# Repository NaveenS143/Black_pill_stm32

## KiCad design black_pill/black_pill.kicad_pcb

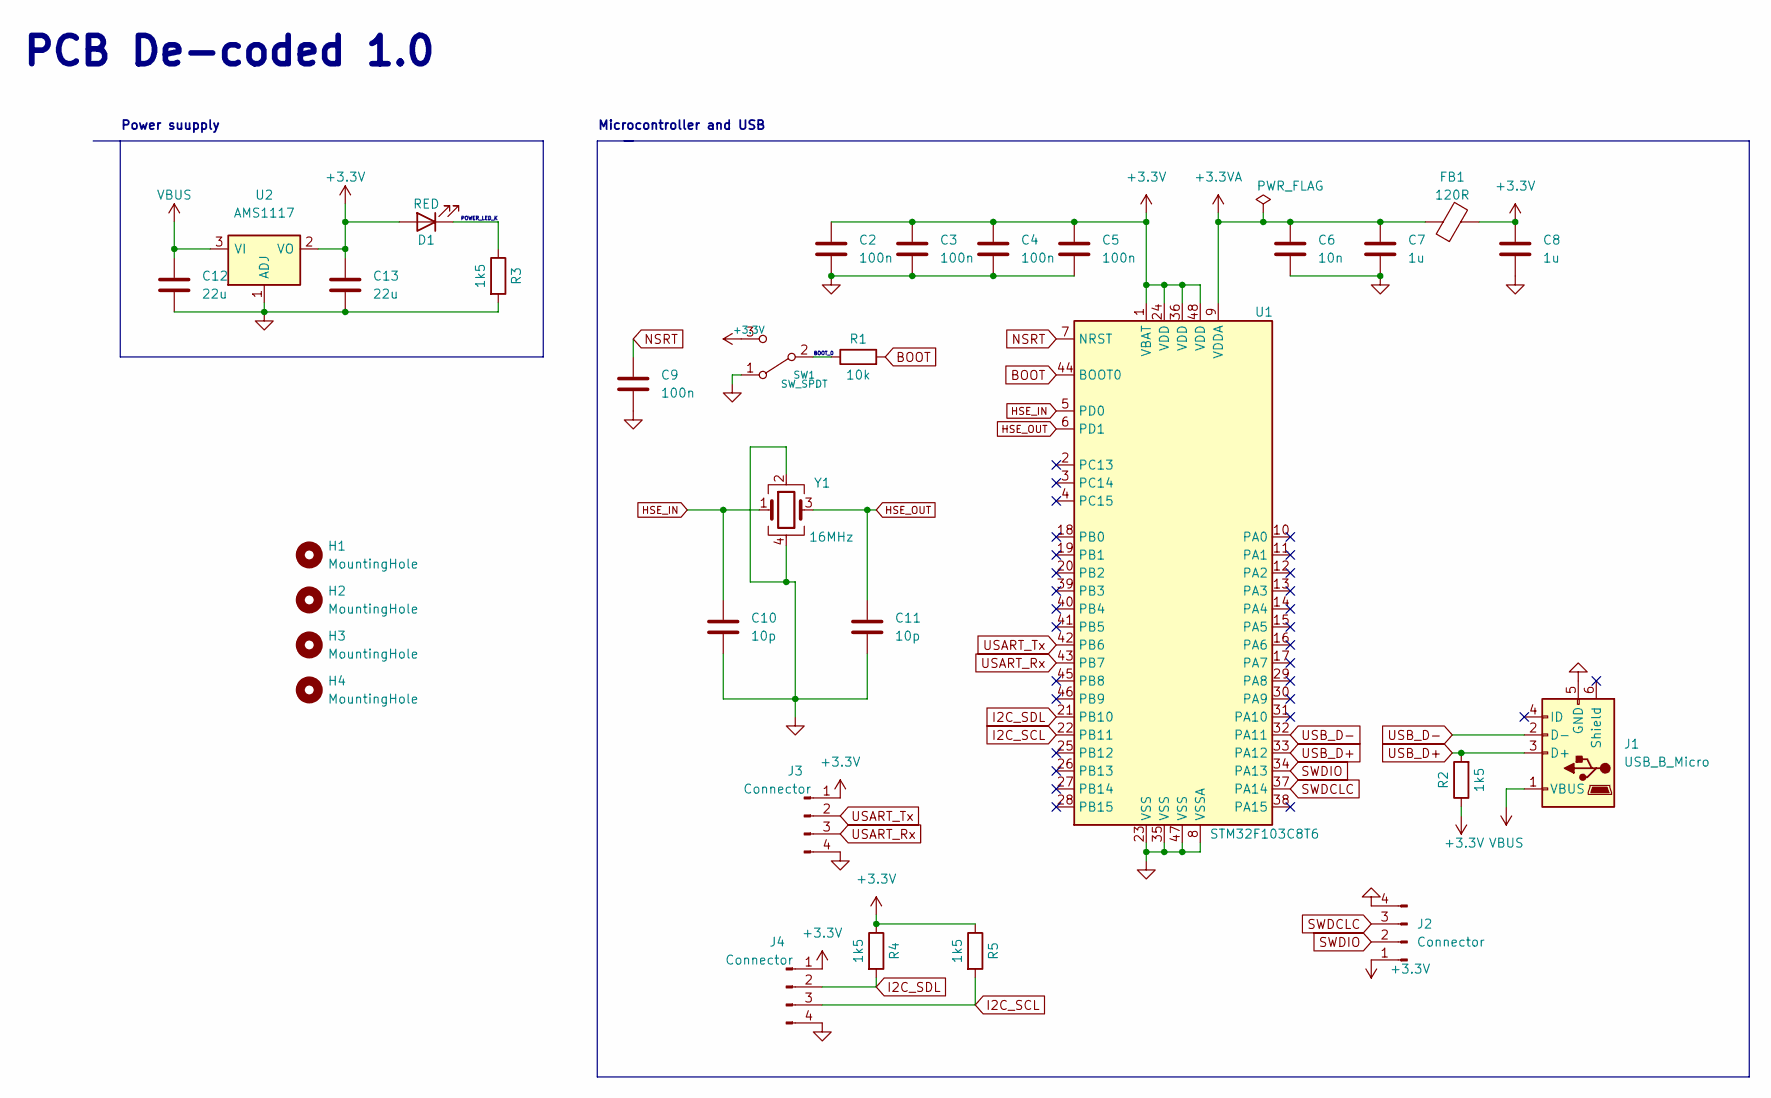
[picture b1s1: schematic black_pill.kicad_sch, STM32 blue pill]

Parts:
C2, C3, C4, C5, C9: 100n; C_0402_1005Metric
C6: 10n; C_0402_1005Metric
C7, C8: 1u; C_0402_1005Metric
C10, C11: 10p; C_0402_1005Metric
C12, C13: 22u; C_0805_2012Metric
D1: RED; LED_0603_1608Metric
FB1: 120R; L_0603_1608Metric
H1, H2, H3, H4: MountingHole; MountingHole_2.2mm_M2
J1: USB_B_Micro; USB_Micro-B_Wuerth_629105150521
J2, J3, J4: Connector; PinHeader_1x04_P2.54mm_Vertical
R1: 10k; R_0402_1005Metric
R2, R3, R4, R5: 1k5; R_0402_1005Metric
SW1: SW_SPDT; SW_SPDT_PCM12
U1: STM32F103C8T6; LQFP-48_7x7mm_P0.5mm
U2: AMS1117; SOT-223-3_TabPin2
Y1: 16MHz; Crystal_SMD_3225-4Pin_3.2x2.5mm

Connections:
+3.3VA: C6.1, C7.1, FB1.1, U1.9 (VDDA)
+3V3: C2.1, C3.1, C4.1, C5.1, C8.1, C13.1, D1.2 (A), FB1.2, J2.1, J3.1, J4.1, R2.1, R4.1, R5.1, SW1.3 (C), U1.1 (VBAT), U1.24 (VDD), U1.36 (VDD), U1.48 (VDD), U2.2 (VO)
BOOT: R1.2, U1.44 (BOOT0)
GND: C2.2, C3.2, C4.2, C5.2, C6.2, C7.2, C8.2, C9.2, C10.2, C11.2, C12.2, C13.2, J1.5 (GND), J2.4, J3.4, J4.4, R3.2, SW1.1 (A), U1.8 (VSSA), U1.23 (VSS), U1.35 (VSS), U1.47 (VSS), U2.1 (ADJ), Y1.2, Y1.4
HSE_IN: C10.1, U1.5 (PD0), Y1.1
HSE_OUT: C11.1, U1.6 (PD1), Y1.3
I2C_SCL: J4.3, R5.2, U1.22 (PB11)
I2C_SDL: J4.2, R4.2, U1.21 (PB10)
NSRT: C9.1, U1.7 (NRST)
unnamed: D1.1 (K), R3.1
unnamed: R1.1, SW1.2 (B)
SWDCLC: J2.3, U1.37 (PA14)
SWDIO: J2.2, U1.34 (PA13)
USART_Rx: J3.3, U1.43 (PB7)
USART_Tx: J3.2, U1.42 (PB6)
USB_D+: J1.3 (D+), R2.2, U1.33 (PA12)
USB_D-: J1.2 (D-), U1.32 (PA11)
VBUS: C12.1, J1.1 (VBUS), U2.3 (VI)

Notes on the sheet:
POWER_LED_K
PCB De-coded 1.0
Microcontroller and USB
BOOT_0
Power suupply

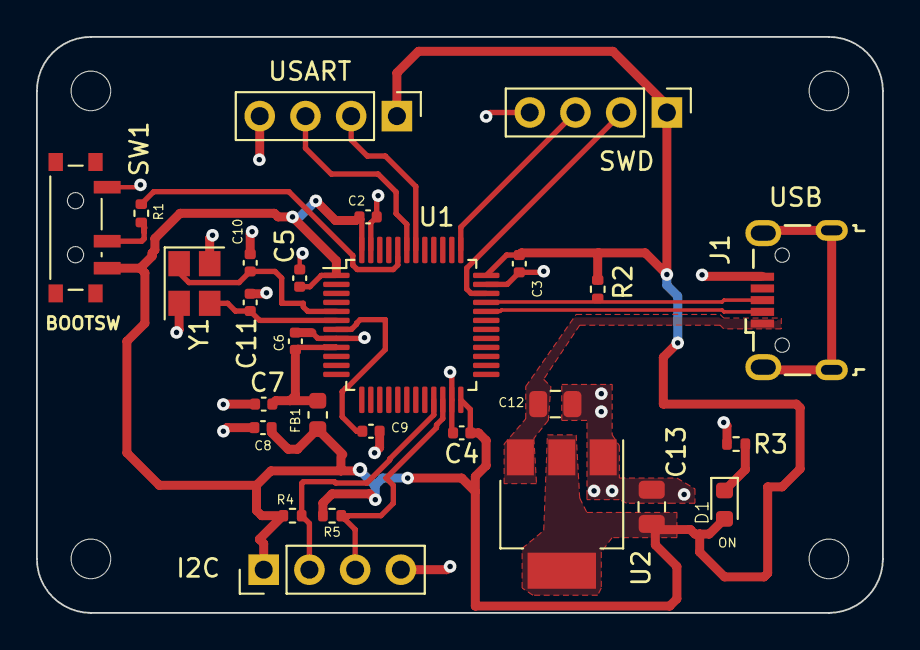
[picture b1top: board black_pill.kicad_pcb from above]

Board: 2 copper layers, 47.0 x 32.0 mm, 31 parts (0 on the bottom side), 18 nets.
